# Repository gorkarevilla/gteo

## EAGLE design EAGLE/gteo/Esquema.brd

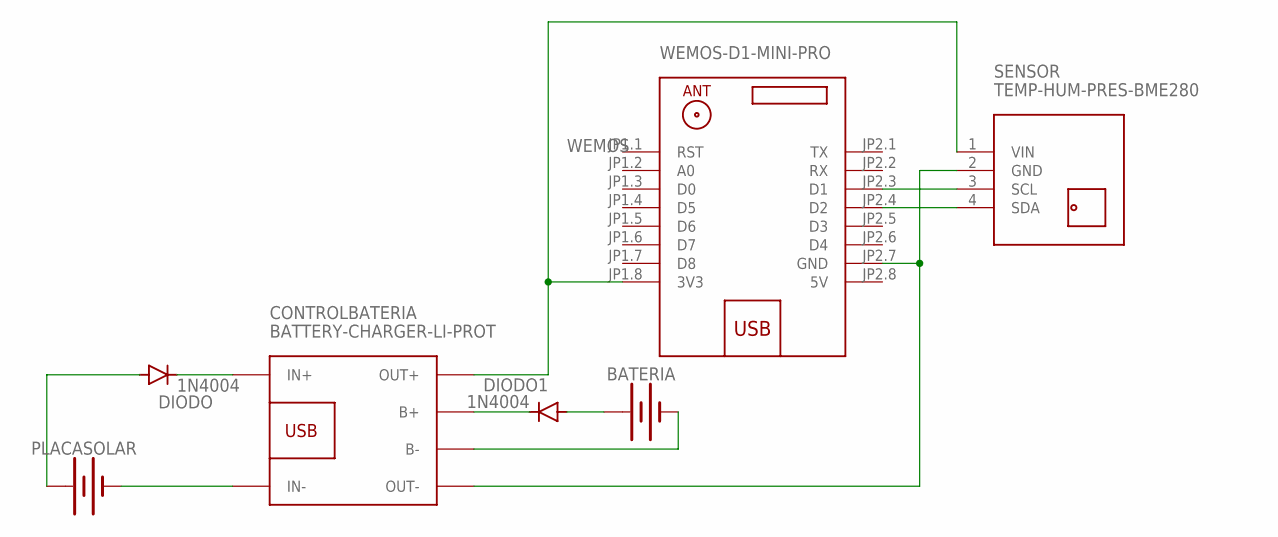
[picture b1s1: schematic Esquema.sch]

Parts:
BATERIA: BATTERY-18650; BATTERY_18650-HOLDER
CONTROLBATERIA: BATTERY-CHARGER-LI-PROT
DIODO, DIODO1: 1N4004; DO41-10
PLACASOLAR: BATTERY-20MM_SMD; BATTCON_20MM
SENSOR: TEMP-HUM-PRES-BME280
WEMOS: WEMOS-D1-MINI-PRO

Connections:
5V: WEMOS.JP2.8 (5V)
unnamed: CONTROLBATERIA.OUT-, SENSOR.2 (GND), WEMOS.JP2.7 (GND)
unnamed: CONTROLBATERIA.IN+, DIODO.C
unnamed: DIODO.A, PLACASOLAR.1 (+)
unnamed: CONTROLBATERIA.IN-, PLACASOLAR.2 (-)
unnamed: BATERIA.PWR@1 (+), DIODO1.A
unnamed: BATERIA.GND@1 (-), CONTROLBATERIA.B-
unnamed: CONTROLBATERIA.B+, DIODO1.C
unnamed: CONTROLBATERIA.OUT+, SENSOR.1 (VIN), WEMOS.JP1.8 (3V3)
unnamed: SENSOR.3 (SCL), WEMOS.JP2.3 (D1)
unnamed: SENSOR.4 (SDA), WEMOS.JP2.4 (D2)

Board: 2 copper layers, 7 parts (0 on the bottom side), 10 nets, no tracks yet.

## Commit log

2018-11-28 doc: add schemas and create structure
2018-11-28 feat: add travis file
2018-11-28 feat: remove ln
2018-11-28 feat: fix file
2018-11-28 feat: add wemos board
2018-11-28 feat: add http
2018-11-28 feat: add prefs
2018-11-28 feat: add prefs2
2018-11-28 feat: add prefs3
2018-11-28 feat: switch board
2018-11-28 feat: switch d1
2018-11-28 feat: switch -v
2018-11-28 feat: remove board
2018-11-28 feat: add board
2018-11-28 feat: switch to generic
2018-11-28 feat: switch to 1.8.0 version
2018-11-28 feat: switch to 2.3.0
2018-11-28 feat: switch to version
2018-11-28 feat: switch to version 2.3.0
2018-11-28 feat: switch to version 2.4.0
2018-11-28 feat: switch to version 2.4.0-rc1
2018-11-28 feat: switch to version 2.2.0
2018-11-28 feat: copy version
2018-11-28 feat: restore version
2018-11-28 feat: fix flash_ld
2018-11-28 feat: fix sudoç
2018-11-28 feat: remove echo
2018-11-28 feat: set last version
2018-11-28 feat: try new compiler
2018-11-28 feat: add adafruit
2018-11-28 feat: remove unused
2018-11-28 feat: add missing packages
2018-11-28 feat: clean packages
2018-11-28 feat: only run in esp8266
2018-11-28 feat: fix readme
2018-12-02 feat: get sensor info
2018-12-14 feat: add led signals
2018-12-15 feat: fix prints
2018-12-15 feat: switch time
2019-01-01 feat: add 3d model

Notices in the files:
parts and their libraries:
SparkFun-Batteries: Licensing: Creative Commons ShareAlike 4.0 International - https://creativecommons.org/licenses/by-sa/4.0
diy-modules: Released under the Creative Commons Attribution 4.0 International License: http://creativecommons.org/licenses/by/4.0
